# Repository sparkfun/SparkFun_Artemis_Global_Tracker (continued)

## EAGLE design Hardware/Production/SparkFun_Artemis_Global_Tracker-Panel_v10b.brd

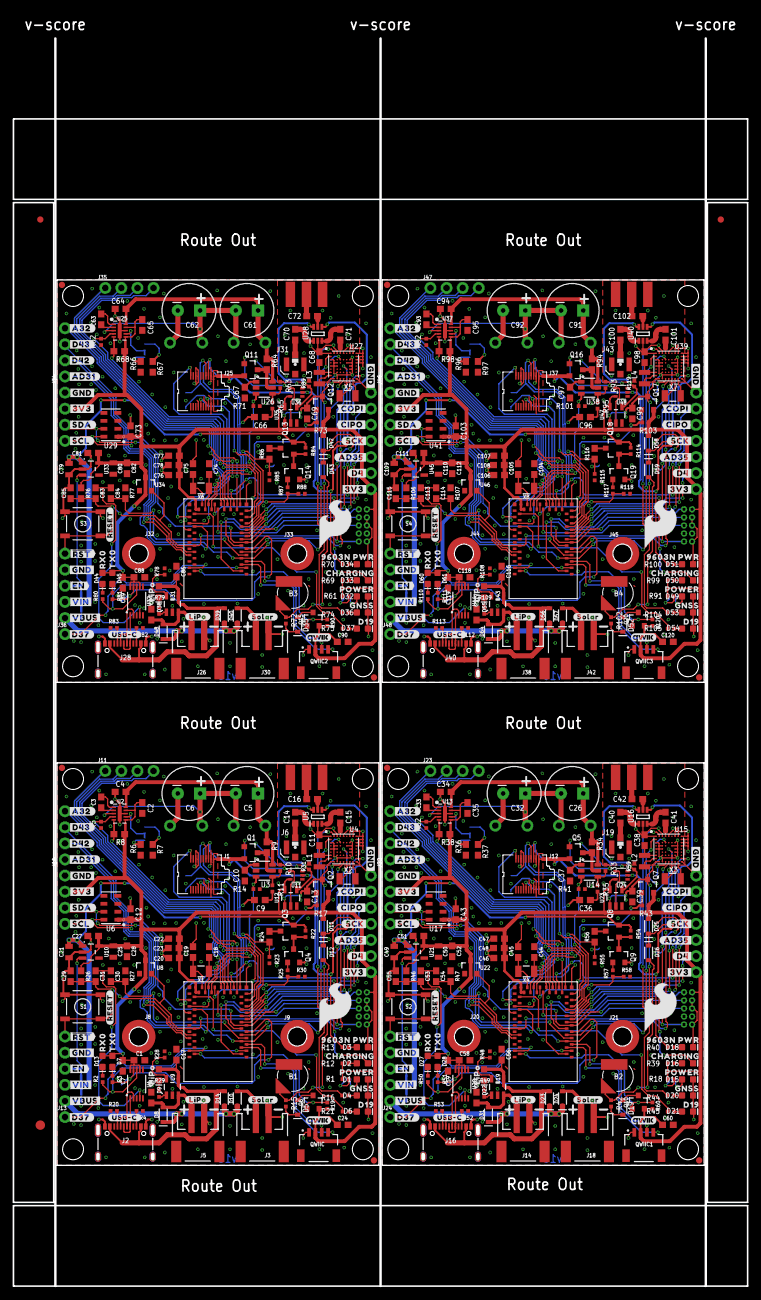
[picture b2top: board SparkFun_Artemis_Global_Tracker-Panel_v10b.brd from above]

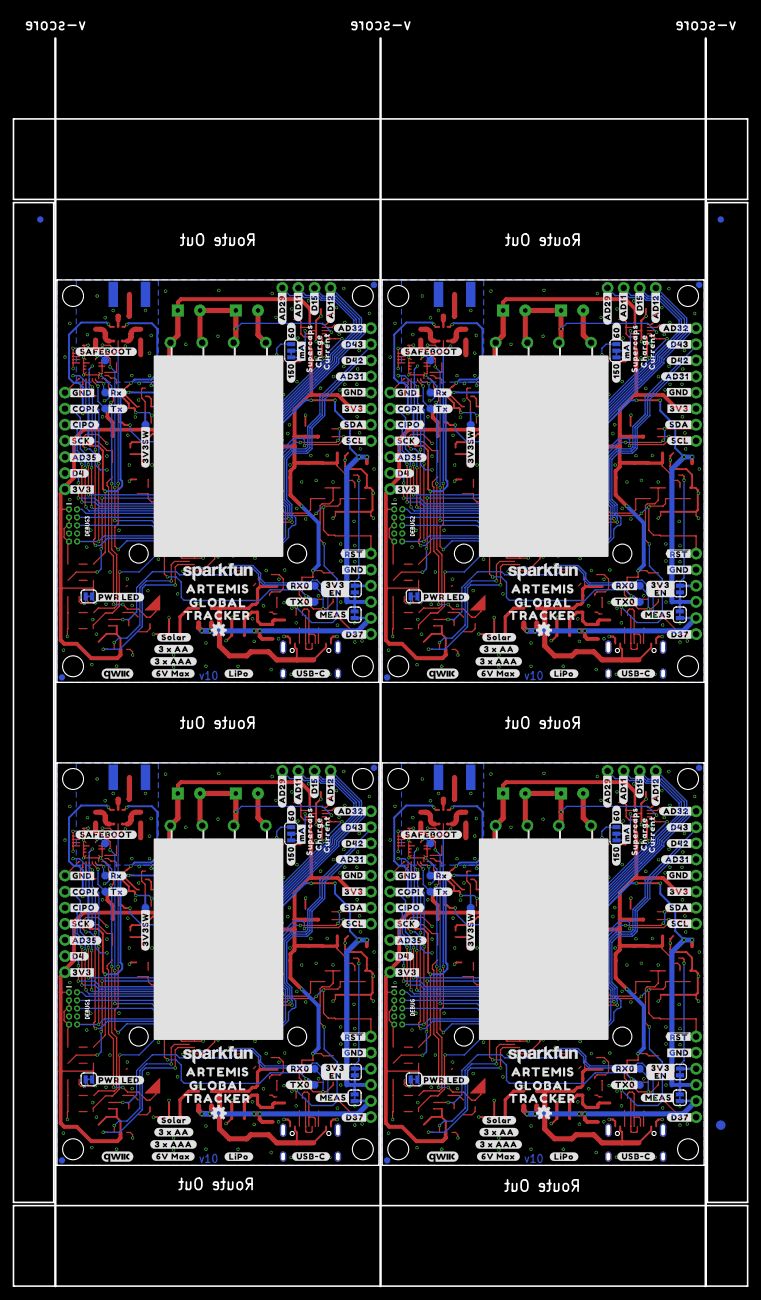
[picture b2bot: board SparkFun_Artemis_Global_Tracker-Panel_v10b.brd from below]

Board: 2 copper layers, 115.8 x 196.9 mm, 958 parts (319 on the bottom side), 404 nets.

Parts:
3V3EN, 3V3EN1, 3V3EN2, 3V3EN3: JUMPER-SMT_2_NC_TRACE_SILK; SMT-JUMPER_2_NC_TRACE_SILK
3V3SW, 3V3SW1, 3V3SW2, 3V3SW3: PAD.03X.05
5V1, 5V2, 5V3, 5V4: TEST-POINT3X5; PAD.03X.05
!RESET, !RESET1, !RESET2, !RESET3: 1X01_NO_SILK
B1, B2, B3, B4: ML414H_IV01E_BATTERY; ML414H_IV01E
C1, C9, C36, C58, C66, C88, C96, C118: 10nF; 0603
C2, C35, C65, C95: 2.2uF; 0603
C3, C10, C23, C24, C27, C33, C37, C48, C51, C60, C63, C67, C78, C81, C90, C93, C97, C108, C111, C120: 1.0uF; 0603
C4, C12, C34, C43, C64, C73, C94, C103: 0.22uF; 0603
C5, C6, C26, C32, C61, C62, C91, C92: 1F 2.7V; CPOL-RADIAL-1F-2.7V
C7, C13, C20, C28, C30, C31, C39, C46, C52, C53, C54, C59, C69, C76, C82, C83, C84, C89, C99, C106, C112, C113, C114, C119: 0.1uF; 0603
C8, C11, C17, C38, C56, C57, C68, C86, C87, C98, C116, C117: 4.7uF; 0603
C14, C15, C16, C40, C41, C42, C70, C71, C72, C100, C101, C102: 100pF; 0603
C18, C19, C44, C45, C74, C75, C104, C105: 15pF; 0603
C21, C25, C49, C50, C79, C80, C109, C110: 22uF; 0805
C22, C47, C77, C107: 10uF; 0603
C29, C55, C85, C115: 1nF; 0603
D1, D7, D15, D28, D32, D45, D49, D61: GREEN; LED-0603
D2, D9, D13, D16, D22, D27, D33, D38, D44, D50, D55, D60: Yellow; LED-0603
D3, D18, D34, D51: RED; LED-0603
D4, D20, D36, D53: BLUE; LED-0603
D5, D8, D10, D11, D12, D14, D19, D23, D24, D25, D26, D31, D35, D39, D40, D42, D43, D48, D52, D56, D57, D58, D59, D64: 0.5A/40V/420mV; SOD-323
D6, D21, D37, D54: WHITE; LED-0603
D17, D29, D30, D41, D46, D47, D62, D63: PAD.03X.05
DEBUG, DEBUG1, DEBUG2, DEBUG3: CORTEX_DEBUG; 2X5-PTH-1.27MM-NO_SILK
E$1, E$2, E$3, E$4: FIDUCIAL-1X2
E$5, E$6: FIDUCIAL-1.5X3
EN, EN1, EN2, EN3: 1X01_NO_SILK
GND, GND1, GND2, GND3: 1X01_NO_SILK
GPS_RX, GPS_RX1, GPS_RX2, GPS_RX3: TEST-POINT3X5; PAD.03X.05
GPS_TX, GPS_TX1, GPS_TX2, GPS_TX3: TEST-POINT3X5; PAD.03X.05
I2C, I2C1, I2C2, I2C3: PTH; 1X04_NO_SILK
J1, J12, J25, J37: IRIDIUM_9603N
J2, J16, J28, J40: USB-C; USB-C-16P-2LAYER-PADS
J3, J5, J14, J18, J26, J30, J38, J42: JST-2-SMD
J4, J15, J27, J39: 1X02_NO_SILK
J6, J19, J31, J43: U.FL
J7, J17, J29, J41: ANTENNA-GROUNDEDEDGE_SMA; SMA-EDGE
J8, J9, J20, J21, J32, J33, J44, J45: STAND-OFF-REFLOW-M2.0_6.0MM_TALL; STAND-OFF-REFLOW-M2.0
J10, J11, J22, J23, J34, J35, J46, J47: 1X04_NO_SILK
J13, J24, J36, J48: 1X01_NO_SILK
JP1, JP15, JP25, JP35: JUMPER-SMT_3_1-NC_TRACE_SILK; SMT-JUMPER_3_1-NC_TRACE_SILK
JP2, JP16, JP26, JP36: JUMPER-SMT_2_NC_TRACE_SILK; SMT-JUMPER_2_NC_TRACE_SILK
JP3, JP4, JP5, JP6, JP7, JP8, JP13, JP14, JP21, JP22, JP23, JP24, JP31, JP32, JP33, JP34: FIDUCIAL1X2; FIDUCIAL-1X2
JP9, JP10, JP11, JP12, JP17, JP18, JP19, JP20, JP27, JP28, JP29, JP30, JP37, JP38, JP39, JP40: STAND-OFF
L1, L2, L3, L4: 2.2uH; 0806
LOGO1, LOGO5, LOGO8, LOGO11: SFE_LOGO_NAME.1_INCH; SFE_LOGO_NAME_.1
LOGO2, LOGO6, LOGO9, LOGO12: SFE_LOGO_FLAME.3_INCH; SFE_LOGO_FLAME_.3
LOGO3, LOGO4, LOGO7, LOGO10: OSHW-LOGOMINI; OSHW-LOGO-MINI
MEAS, MEAS1, MEAS2, MEAS3: JUMPER-SMT_2_NC_TRACE_SILK; SMT-JUMPER_2_NC_TRACE_SILK
Q1, Q5, Q11, Q16: 5.8A/30V/35mΩ; SOT23-3
Q2, Q3, Q6, Q7, Q8, Q10, Q12, Q13, Q15, Q17, Q18, Q20: 20V/4.2A/52mΩ/1.4W; SOT23-3
Q4, Q9, Q14, Q19: 600mA/40V; SOT23-3
QWIIC, QWIIC1, QWIIC2, QWIIC3: QWIIC_RA; JST04_1MM_RA
R1, R18, R61, R91: 330; 0402-TIGHT
R2, R3, R12, R16, R21, R25, R29, R39, R44, R45, R49, R50, R51, R57, R69, R74, R75, R79, R80, R81, R87, R99, R104, R105, R109, R110, R111, R117: 1k; 0402-TIGHT
R4, R20, R52, R53, R82, R83, R112, R113: 5.1k; 0402-TIGHT
R5, R14, R17, R19, R22, R23, R30, R32, R41, R43, R54, R55, R58, R60, R62, R71, R73, R84, R85, R88, R90, R92, R101, R103, R114, R115, R118, R120: 10K; 0402-TIGHT
R6, R36, R66, R96: 12k; 0603
R7, R37, R67, R97: 30.1k; 0603
R8, R26, R38, R46, R68, R76, R98, R106: 100k; 0603
R9, R34, R64, R94: 0.015ohm; 0603
R10, R11, R33, R35, R63, R65, R93, R95: 100; 0402-TIGHT
R13, R28, R40, R48, R70, R78, R100, R108: 2.0K; 0402-TIGHT
R15, R42, R72, R102: 3.3K; 0402-TIGHT
R24, R56, R86, R116: 20k; 0603
R27, R47, R77, R107: 220k; 0603
R31, R59, R89, R119: 20k; 0402-TIGHT
RX0, RX1, RX2, RX3, RX4, RX5, RX6, RX7: TEST-POINT3X5; PAD.03X.05
S1, S2, S3, S4: RESET; TACTILE_SWITCH_SMD_5.2MM
SAFEBOOT, SAFEBOOT1, SAFEBOOT2, SAFEBOOT3: TEST-POINT3X5; PAD.03X.05
SC1+, SC1+1, SC1+2, SC1+3, SC1-, SC1-1, SC1-2, SC1-3, SC2+, SC2+1, SC2+2, SC2+3, SC2-, SC2-1, SC2-2, SC2-3: 1X01_NO_SILK
SPI, SPI1, SPI2, SPI3: 1X07_NO_SILK
TX0, TX1, TX2, TX3, TX4, TX5, TX6, TX7: TEST-POINT3X5; PAD.03X.05
U1, U20, U32, U44: CH340E_MSOP10; MSOP10
U2, U13, U25, U37: LTC3225EDDB; DFN300X200-10L
U3, U14, U26, U38: ADM4210_1TSOT6; TSOT6
U4, U15, U27, U39: U-BLOX_ZOE_M8Q-0-10; UBLOX_ZOE_M8-0-10
U5, U16, U28, U40: AS179-92LF; SOT65P220X100-6N
U6, U17, U29, U41: MS8607-02BA01
U7, U18, U30, U42: ARTEMIS_MODULESMD; ARTEMIS_FP
U8, U22, U34, U46: V_SUPERVISOR_BD48K24G_2.4V; SOT23-3
U9, U19, U31, U43: MCP73831; SOT23-5
U10, U21, U33, U45: 3.3V; SOT23-5
U11, U24, U36, U48: 74LVC1G04SE; SOT353
U12, U23, U35, U47: 74LVC1G08W5-7; SOT23-5
U$1, U$13, U$131, U$132, U$223, U$224, U$315, U$316: SUPERCAPACITOR151
U$2, U$177, U$269, U$361: #SCK#199608
U$3, U$43, U$111, U$124, U$203, U$216, U$295, U$308: #3V3#0
U$4, U$112, U$204, U$296: #SDA#0
U$5, U$117, U$209, U$301: #USB#C#0
U$6, U$113, U$205, U$297: #SCL#0
U$7, U$143, U$235, U$327: #VIN#158
U$8, U$98, U$190, U$282: #3V3SW#0
U$9, U$173, U$265, U$357: CHARGING9604
U$10, U$149, U$241, U$333: #COPI#9694
U$11, U$23, U$185, U$277: QWIIC_4MM
U$12, U$182, U$274, U$366: LIPO5
U$14, U$15, U$133, U$134, U$225, U$226, U$317, U$318: 10F_2#7V152
U$16, U$183, U$275, U$367: RX06
U$17, U$70, U$138, U$151, U$230, U$243, U$322, U$335: #3V3#153
U$18, U$184, U$276, U$368: TX07
U$19, U$178, U$270, U$362: #AD35#199609
U$20, U$36, U$110, U$125, U$202, U$217, U$294, U$309: #GND#0
U$21, U$139, U$231, U$323: #SDA#153
U$22, U$140, U$232, U$324: #SCL#154
U$24, U$152, U$244, U$336: #AD31#7
U$25, U$49, U$186, U$278: QWIIC_5MM
U$26, U$141, U$233, U$325: #_RST##156
U$27, U$142, U$234, U$326: #EN#157
U$28, U$99, U$191, U$283: #VIN#3#0
U$29, U$179, U$271, U$363: #AD35#0
U$30, U$62, U$187, U$279: ARTEMIS0
U$31, U$128, U$220, U$312: SUPERCAPS6
U$32, U$101, U$193, U$285: #D17#0
U$33, U$109, U$201, U$293: #SAFEBOOT#0
U$34, U$104, U$196, U$288: #TX0#0
U$35, U$106, U$198, U$290: #TX1#0
U$37, U$108, U$200, U$292: #RX#0
U$38, U$105, U$197, U$289: #RX1#0
U$39, U$107, U$199, U$291: #TX#0
U$40, U$100, U$192, U$284: #5#3V#0
U$41, U$102, U$194, U$286: #D41#0
U$42, U$103, U$195, U$287: #RX0#0
U$44, U$146, U$238, U$330: #RESET#162
U$45, U$148, U$240, U$332: #SOLAR#165
U$46, U$147, U$239, U$331: #LIPO#164
U$47, U$114, U$206, U$298: #MEAS#0
U$48, U$115, U$207, U$299: #3V3_#0
U$50, U$180, U$272, U$364: #D4#36
U$51, U$68, U$188, U$280: GLOBAL0
U$52, U$97, U$189, U$281: TRACKER0
U$53, U$118, U$210, U$302: #LIPO#0
U$54, U$116, U$208, U$300: #_EN_#0
U$55, U$119, U$211, U$303: #SOLAR#0
U$56, U$145, U$237, U$329: #USB#C#161
U$57, U$120, U$212, U$304: #3_X_AA#0
U$58, U$144, U$236, U$328: #VBUS#159
U$59, U$167, U$259, U$351: #AD32#152
U$60, U$150, U$242, U$334: #SCK#9696
U$61, U$123, U$215, U$307: #PWR_LED#0
U$63, U$181, U$273, U$365: #D4#5
U$64, U$126, U$218, U$310: #CIPO#2
U$65, U$121, U$213, U$305: #3_X_AAA#0
U$66, U$122, U$214, U$306: #6V_MAX#0
U$67, U$129, U$221, U$313: CHARGE8
U$69, U$130, U$222, U$314: CURRENT9
U$71, U$153, U$245, U$337: #D42#32
U$72, U$168, U$260, U$352: #D37#152
U$73, U$154, U$246, U$338: #D43#43
U$74, U$158, U$250, U$342: #150#61
U$75, U$127, U$219, U$311: #COPI#5
U$76, U$77, U$78, U$135, U$136, U$137, U$227, U$228, U$229, U$319, U$320, U$321: #GND#152
U$79, U$155, U$247, U$339: #A32#44
U$80, U$156, U$248, U$340: #MA#45
U$81, U$157, U$249, U$341: #60#46
U$82, U$159, U$251, U$343: #D43#151
U$83, U$160, U$252, U$344: #D42#151
U$84, U$161, U$253, U$345: #AD31#151
U$85, U$162, U$254, U$346: #AD12#151
U$86, U$163, U$255, U$347: #D15#151
U$87, U$164, U$256, U$348: #AD11#151
U$88, U$165, U$257, U$349: #AD29#151
U$89, U$166, U$258, U$350: #CIPO#151
U$90, U$169, U$261, U$353: #D37#0
U$91, U$170, U$262, U$354: #GND#38
U$92, U$171, U$263, U$355: ##RST##39
U$93, U$172, U$264, U$356: 9603N_PWR40
U$94, U$174, U$266, U$358: POWER9605
U$95, U$175, U$267, U$359: GNSS9606
U$96, U$176, U$268, U$360: D199607
VIN/1, VIN/2, VIN/3, VIN/4: TEST-POINT3X5; PAD.03X.05
X1, X2, X3, X4, X5, X6, X7, X8: 32.768kHz; CRYSTAL-SMD-3.2X1.5MM

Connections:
3.3V: C1.1, C2.1, C7.1, C12.1, C20.2, C22.1, C23.1, C24.1, C25.1, C27.1, C28.1, D7.A, D11.A, D13.A, DEBUG.1, I2C.2, Q2.2, Q6.2, QWIIC.2, R1.2, R8.2, R12.2, R17.2, R19.2, R26.2, SPI.7, U1.7, U1.10, U2.6, U2.9, U6.1, U7.VDD@36, U7.VDD@37, U8.3, U10.5, U11.5, U12.5
3.3V1: C35.1, C43.1, C46.2, C47.1, C48.1, C50.1, C51.1, C52.1, C58.1, C59.1, C60.1, D25.A, D27.A, D28.A, DEBUG1.1, I2C1.2, Q7.2, Q10.2, QWIIC1.2, R18.2, R38.2, R39.2, R43.2, R46.2, R60.2, SPI1.7, U13.6, U13.9, U17.1, U18.VDD@36, U18.VDD@37, U20.7, U20.10, U21.5, U22.3, U23.5, U24.5
3.3V2: C65.1, C73.1, C76.2, C77.1, C78.1, C80.1, C81.1, C82.1, C88.1, C89.1, C90.1, D42.A, D44.A, D45.A, DEBUG2.1, I2C2.2, Q12.2, Q15.2, QWIIC2.2, R61.2, R68.2, R69.2, R73.2, R76.2, R90.2, SPI2.7, U25.6, U25.9, U29.1, U30.VDD@36, U30.VDD@37, U32.7, U32.10, U33.5, U34.3, U35.5, U36.5
3.3V3: C95.1, C103.1, C106.2, C107.1, C108.1, C110.1, C111.1, C112.1, C118.1, C119.1, C120.1, D58.A, D60.A, D61.A, DEBUG3.1, I2C3.2, Q17.2, Q20.2, QWIIC3.2, R91.2, R98.2, R99.2, R103.2, R106.2, R120.2, SPI3.7, U37.6, U37.9, U41.1, U42.VDD@36, U42.VDD@37, U44.7, U44.10, U45.5, U46.3, U47.5, U48.5
3V3SW: 3V3SW.1, C13.1, Q2.3, R16.2, U4.24, U4.25, U12.1
3V3SW1: 3V3SW1.1, C39.1, Q7.3, R44.2, U15.24, U15.25, U23.1
3V3SW2: 3V3SW2.1, C69.1, Q12.3, R74.2, U27.24, U27.25, U35.1
3V3SW3: 3V3SW3.1, C99.1, Q17.3, R104.2, U39.24, U39.25, U47.1
ANTENNA: C16.1, J7.SIG
ANTENNA1: C42.1, J17.SIG
ANTENNA2: C72.1, J29.SIG
ANTENNA3: C102.1, J41.SIG
ARTEMIS_!RESET: !RESET.1, C29.1, C31.2, DEBUG.10, R26.1, S1.3, S1.4, U4.20, U7.~RST, U8.2
ARTEMIS_!RESET1: !RESET1.1, C53.2, C55.1, DEBUG1.10, R46.1, S2.3, S2.4, U15.20, U18.~RST, U22.2
ARTEMIS_!RESET2: !RESET2.1, C83.2, C85.1, DEBUG2.10, R76.1, S3.3, S3.4, U27.20, U30.~RST, U34.2
ARTEMIS_!RESET3: !RESET3.1, C113.2, C115.1, DEBUG3.10, R106.1, S4.3, S4.4, U39.20, U42.~RST, U46.2
ARTEMIS_!RTS!: C30.1, C31.1, U1.4
ARTEMIS_!RTS!1: C53.1, C54.1, U20.4
ARTEMIS_!RTS!2: C83.1, C84.1, U32.4
ARTEMIS_!RTS!3: C113.1, C114.1, U44.4
ARTEMIS_AD1: J22.1, U18.~AD31
ARTEMIS_AD2: J23.4, U18.~AD29
ARTEMIS_AD3: J23.3, U18.~AD11
ARTEMIS_AD4: J23.1, U18.~AD12
ARTEMIS_AD5: J22.4, U18.~AD32
ARTEMIS_AD6: J34.1, U30.~AD31
ARTEMIS_AD7: J35.4, U30.~AD29
ARTEMIS_AD8: J35.3, U30.~AD11
ARTEMIS_AD9: J35.1, U30.~AD12
ARTEMIS_AD10: J34.4, U30.~AD32
ARTEMIS_AD11: J11.3, U7.~AD11
ARTEMIS_AD12: J11.1, U7.~AD12
ARTEMIS_AD13: J46.1, U42.~AD31
ARTEMIS_AD14: J47.4, U42.~AD29
ARTEMIS_AD15: J47.3, U42.~AD11
ARTEMIS_AD16: J47.1, U42.~AD12
ARTEMIS_AD17: J46.4, U42.~AD32
ARTEMIS_AD29: J11.4, U7.~AD29
ARTEMIS_AD31: J10.1, U7.~AD31
ARTEMIS_AD32: J10.4, U7.~AD32
ARTEMIS_BOOT: C30.2, R27.2, U7.BOOT
ARTEMIS_BOOT1: C54.2, R47.2, U18.BOOT
ARTEMIS_BOOT2: C84.2, R77.2, U30.BOOT
ARTEMIS_BOOT3: C114.2, R107.2, U42.BOOT
ARTEMIS_D1: DEBUG1.6, U18.~AD33/SWO
ARTEMIS_D2: SPI1.5, U18.~AD35
ARTEMIS_D3: R55.1, R56.2, U18.~AD13, VIN/1.1
ARTEMIS_D4: SPI.6, U7.~D4
ARTEMIS_D5: R45.2, U18.~D19
ARTEMIS_D5_SCK: SPI.4, U7.~D5
ARTEMIS_D5_SCK1: SPI1.4, U18.~D5
ARTEMIS_D5_SCK2: SPI2.4, U30.~D5
ARTEMIS_D5_SCK3: SPI3.4, U42.~D5
ARTEMIS_D6: J12.19, U18.~D18
ARTEMIS_D6_MISO: SPI.3, U7.~D6
ARTEMIS_D6_MISO1: SPI1.3, U18.~D6
ARTEMIS_D6_MISO2: SPI2.3, U30.~D6
ARTEMIS_D6_MISO3: SPI3.3, U42.~D6
ARTEMIS_D7: J12.7, RX3.1, U18.~D25
ARTEMIS_D7_MOSI: SPI.2, U7.D7
ARTEMIS_D7_MOSI1: SPI1.2, U18.D7
ARTEMIS_D7_MOSI2: SPI2.2, U30.D7
ARTEMIS_D7_MOSI3: SPI3.2, U42.D7
ARTEMIS_D8: R32.2, U13.4, U18.~D27
ARTEMIS_D8_SCL: I2C.4, U4.32, U6.8, U7.D8
ARTEMIS_D8_SCL1: I2C1.4, U15.32, U17.8, U18.D8
ARTEMIS_D8_SCL2: I2C2.4, U27.32, U29.8, U30.D8
ARTEMIS_D8_SCL3: I2C3.4, U39.32, U41.8, U42.D8
ARTEMIS_D9: SPI1.6, U18.~D4
ARTEMIS_D9_SDA: I2C.3, U4.2, U6.7, U7.D9
ARTEMIS_D9_SDA1: I2C1.3, U15.2, U17.7, U18.D9
ARTEMIS_D9_SDA2: I2C2.3, U27.2, U29.7, U30.D9
ARTEMIS_D9_SDA3: I2C3.3, U39.2, U41.7, U42.D9
ARTEMIS_D10: U4.50, U7.D10
ARTEMIS_D11: U15.50, U18.D10
ARTEMIS_D12: D29.1, J12.5, U18.D17
ARTEMIS_D13: R23.1, R24.2, U7.~AD13, VIN/3.1
ARTEMIS_D14: R41.1, U14.3, U18.~D22
ARTEMIS_D15: J11.2, U7.D15
ARTEMIS_D16: J12.6, TX3.1, U18.~D24
ARTEMIS_D17: D17.1, J1.5, U7.D17
ARTEMIS_D18: J1.19, U7.~D18
ARTEMIS_D19: R21.2, U7.~D19
ARTEMIS_D20: Q7.1, R43.1, U18.~D26
ARTEMIS_D21: D16.C, R38.1, U13.5, U18.~D28
ARTEMIS_D22: R14.1, U3.3, U7.~D22
ARTEMIS_D23: D30.1, J12.12, U18.D41
ARTEMIS_D24: J1.6, TX1.1, U7.~D24
ARTEMIS_D25: J1.7, RX1.1, U7.~D25
ARTEMIS_D26: Q2.1, R17.1, U7.~D26
ARTEMIS_D27: R5.2, U2.4, U7.~D27
ARTEMIS_D28: D2.C, R8.1, U2.5, U7.~D28
ARTEMIS_D29: R57.1, R58.1, U18.AD34
ARTEMIS_D30: Q10.1, R60.1, U18.~D44
ARTEMIS_D31: J22.2, U18.~D42
ARTEMIS_D32: J22.3, U18.~D43
ARTEMIS_D33: DEBUG.6, U7.~AD33/SWO
ARTEMIS_D34: R25.1, R30.1, U7.AD34
ARTEMIS_D35: SPI.5, U7.~AD35
ARTEMIS_D36: J23.2, U18.D15
ARTEMIS_D37: J13.1, U7.~D37
ARTEMIS_D38: J24.1, U18.~D37
ARTEMIS_D39: DEBUG2.6, U30.~AD33/SWO
ARTEMIS_D39_SCL1: QWIIC1.4, U18.~D39
ARTEMIS_D39_SCL2: QWIIC2.4, U30.~D39
ARTEMIS_D39_SCL3: QWIIC3.4, U42.~D39
ARTEMIS_D39_SCL4: QWIIC.4, U7.~D39
ARTEMIS_D40: SPI2.5, U30.~AD35
ARTEMIS_D40_SDA1: QWIIC1.3, U18.D40
ARTEMIS_D40_SDA2: QWIIC2.3, U30.D40
ARTEMIS_D40_SDA3: QWIIC3.3, U42.D40
ARTEMIS_D40_SDA4: QWIIC.3, U7.D40
ARTEMIS_D41: D41.1, J1.12, U7.D41
ARTEMIS_D42: J10.2, U7.~D42
ARTEMIS_D43: J10.3, U7.~D43
ARTEMIS_D44: Q6.1, R19.1, U7.~D44
ARTEMIS_D45: R85.1, R86.2, U30.~AD13, VIN/2.1
ARTEMIS_D46: R75.2, U30.~D19
ARTEMIS_D47: J25.19, U30.~D18
ARTEMIS_D48: J25.7, RX5.1, U30.~D25
ARTEMIS_D49: R62.2, U25.4, U30.~D27
ARTEMIS_D50: SPI2.6, U30.~D4
ARTEMIS_D51: U27.50, U30.D10
ARTEMIS_D52: D46.1, J25.5, U30.D17
ARTEMIS_D53: R71.1, U26.3, U30.~D22
ARTEMIS_D54: J25.6, TX5.1, U30.~D24
ARTEMIS_D55: Q12.1, R73.1, U30.~D26
ARTEMIS_D56: D33.C, R68.1, U25.5, U30.~D28
ARTEMIS_D57: D47.1, J25.12, U30.D41
ARTEMIS_D58: R87.1, R88.1, U30.AD34
ARTEMIS_D59: Q15.1, R90.1, U30.~D44
ARTEMIS_D60: J34.2, U30.~D42
ARTEMIS_D61: J34.3, U30.~D43
ARTEMIS_D62: J35.2, U30.D15
ARTEMIS_D63: J36.1, U30.~D37
ARTEMIS_D64: DEBUG3.6, U42.~AD33/SWO
ARTEMIS_D65: SPI3.5, U42.~AD35
ARTEMIS_D66: R115.1, R116.2, U42.~AD13, VIN/4.1
ARTEMIS_D67: R105.2, U42.~D19
ARTEMIS_D68: J37.19, U42.~D18
ARTEMIS_D69: J37.7, RX7.1, U42.~D25
ARTEMIS_D70: R92.2, U37.4, U42.~D27
ARTEMIS_D71: SPI3.6, U42.~D4
ARTEMIS_D72: U39.50, U42.D10
ARTEMIS_D73: D62.1, J37.5, U42.D17
ARTEMIS_D74: R101.1, U38.3, U42.~D22
ARTEMIS_D75: J37.6, TX7.1, U42.~D24
ARTEMIS_D76: Q17.1, R103.1, U42.~D26
ARTEMIS_D77: D50.C, R98.1, U37.5, U42.~D28
ARTEMIS_D78: D63.1, J37.12, U42.D41
ARTEMIS_D79: R117.1, R118.1, U42.AD34
ARTEMIS_D80: Q20.1, R120.1, U42.~D44
ARTEMIS_D81: J46.2, U42.~D42
ARTEMIS_D82: J46.3, U42.~D43
ARTEMIS_D83: J47.2, U42.D15
ARTEMIS_D84: J48.1, U42.~D37
ARTEMIS_RX0: R2.1, RX0.1, U1.8, U7.RXI-0
ARTEMIS_RX1: R50.1, RX2.1, U18.RXI-0, U20.8
ARTEMIS_RX2: R80.1, RX4.1, U30.RXI-0, U32.8
ARTEMIS_RX3: R110.1, RX6.1, U42.RXI-0, U44.8
ARTEMIS_SWDCK: DEBUG.4, U7.SWDCK
ARTEMIS_SWDCK1: DEBUG1.4, U18.SWDCK
ARTEMIS_SWDCK2: DEBUG2.4, U30.SWDCK
ARTEMIS_SWDCK3: DEBUG3.4, U42.SWDCK
ARTEMIS_SWDIO: DEBUG.2, U7.SWDIO
ARTEMIS_SWDIO1: DEBUG1.2, U18.SWDIO
ARTEMIS_SWDIO2: DEBUG2.2, U30.SWDIO
ARTEMIS_SWDIO3: DEBUG3.2, U42.SWDIO
ARTEMIS_TX0: R3.1, TX0.1, U1.9, U7.TXO-0
ARTEMIS_TX1: R51.1, TX2.1, U18.TXO-0, U20.9
ARTEMIS_TX2: R81.1, TX4.1, U30.TXO-0, U32.9
ARTEMIS_TX3: R111.1, TX6.1, U42.TXO-0, U44.9
CC1: J16.B5, R52.2
CC2: J16.A5, R53.2
CC3: J2.B5, R4.2
CC4: J2.A5, R20.2
CC5: J28.B5, R82.2
CC6: J28.A5, R83.2
CC7: J40.B5, R112.2
CC8: J40.A5, R113.2
D+1: J16.A6, J16.B6, U20.1
D+2: J2.A6, J2.B6, U1.1
D+3: J28.A6, J28.B6, U32.1
D+4: J40.A6, J40.B6, U44.1
D-1: J16.A7, J16.B7, U20.2
D-2: J2.A7, J2.B7, U1.2
D-3: J28.A7, J28.B7, U32.2
D-4: J40.A7, J40.B7, U44.2
EXT_PWR: 5V3.1, J1.1, J1.2, Q1.2, R13.2, U5.4, U11.2
EXT_PWR1: 5V1.1, J12.1, J12.2, Q5.2, R40.2, U16.4, U24.2
EXT_PWR2: 5V2.1, J25.1, J25.2, Q11.2, R70.2, U28.4, U36.2
EXT_PWR3: 5V4.1, J37.1, J37.2, Q16.2, R100.2, U40.4, U48.2
GND: B1.-, C1.2, C2.2, C4.2, C6.-, C7.2, C8.2, C9.2, C10.2, C11.2, C12.2, C13.2, C17.2, C18.1, C19.1, C20.1, C21.2, C22.2, C23.2, C24.2, C25.2, C27.2, C28.2, C29.2, D1.C, D3.C, D4.C, D6.C, DEBUG.3, DEBUG.5, DEBUG.9, GND.1, I2C.1, J1.3, J1.4, J1.8, J1.13, J1.14, J1.15, J1.18, J2.GND, J2.GND2, J3.1, J5.1, J6.1, J6.2, J7.GND@0, J7.GND@1, J7.GND@2, J7.GND@3, J8.1, J9.1, Q4.2, QWIIC.1, R4.1, R5.1, R6.1, R7.2, R14.2, R20.1, R23.2, R27.1, R28.1, R30.2, R31.2, S1.1, S1.2, SC2-.1, SPI.1, U1.3, U2.8, U2.11, U3.2, U4.1, U4.3, U4.5, U4.7, U4.8, U4.9, U4.10, U4.11, U4.12, U4.17, U4.23, U4.29, U4.31, U4.37, U4.38, U4.39, U4.40, U4.41, U4.44, U4.46, U4.47, U4.49, U5.2, U6.3, U7.GND@1, U7.GND@22, U7.GND@38, U7.GND@39, U7.GND@47, U7.GND@59, U8.1, U9.2, U10.2, U11.3, U12.3
GND1: B2.-, C32.-, C34.2, C35.2, C36.2, C37.2, C38.2, C39.2, C43.2, C44.1, C45.1, C46.1, C47.2, C48.2, C49.2, C50.2, C51.2, C52.2, C55.2, C56.2, C57.2, C58.2, C59.2, C60.2, D15.C, D18.C, D20.C, D21.C, DEBUG1.3, DEBUG1.5, DEBUG1.9, GND1.1, I2C1.1, J12.3, J12.4, J12.8, J12.13, J12.14, J12.15, J12.18, J14.1, J16.GND, J16.GND2, J17.GND@0, J17.GND@1, J17.GND@2, J17.GND@3, J18.1, J19.1, J19.2, J20.1, J21.1, Q9.2, QWIIC1.1, R32.1, R36.1, R37.2, R41.2, R47.1, R48.1, R52.1, R53.1, R55.2, R58.2, R59.2, S2.1, S2.2, SC2-1.1, SPI1.1, U13.8, U13.11, U14.2, U15.1, U15.3, U15.5, U15.7, U15.8, U15.9, U15.10, U15.11, U15.12, U15.17, U15.23, U15.29, U15.31, U15.37, U15.38, U15.39, U15.40, U15.41, U15.44, U15.46, U15.47, U15.49, U16.2, U17.3, U18.GND@1, U18.GND@22, U18.GND@38, U18.GND@39, U18.GND@47, U18.GND@59, U19.2, U20.3, U21.2, U22.1, U23.3, U24.3
GND2: B3.-, C62.-, C64.2, C65.2, C66.2, C67.2, C68.2, C69.2, C73.2, C74.1, C75.1, C76.1, C77.2, C78.2, C79.2, C80.2, C81.2, C82.2, C85.2, C86.2, C87.2, C88.2, C89.2, C90.2, D32.C, D34.C, D36.C, D37.C, DEBUG2.3, DEBUG2.5, DEBUG2.9, GND2.1, I2C2.1, J25.3, J25.4, J25.8, J25.13, J25.14, J25.15, J25.18, J26.1, J28.GND, J28.GND2, J29.GND@0, J29.GND@1, J29.GND@2, J29.GND@3, J30.1, J31.1, J31.2, J32.1, J33.1, Q14.2, QWIIC2.1, R62.1, R66.1, R67.2, R71.2, R77.1, R78.1, R82.1, R83.1, R85.2, R88.2, R89.2, S3.1, S3.2, SC2-2.1, SPI2.1, U25.8, U25.11, U26.2, U27.1, U27.3, U27.5, U27.7, U27.8, U27.9, U27.10, U27.11, U27.12, U27.17, U27.23, U27.29, U27.31, U27.37, U27.38, U27.39, U27.40, U27.41, U27.44, U27.46, U27.47, U27.49, U28.2, U29.3, U30.GND@1, U30.GND@22, U30.GND@38, U30.GND@39, U30.GND@47, U30.GND@59, U31.2, U32.3, U33.2, U34.1, U35.3, U36.3
GND3: B4.-, C92.-, C94.2, C95.2, C96.2, C97.2, C98.2, C99.2, C103.2, C104.1, C105.1, C106.1, C107.2, C108.2, C109.2, C110.2, C111.2, C112.2, C115.2, C116.2, C117.2, C118.2, C119.2, C120.2, D49.C, D51.C, D53.C, D54.C, DEBUG3.3, DEBUG3.5, DEBUG3.9, GND3.1, I2C3.1, J37.3, J37.4, J37.8, J37.13, J37.14, J37.15, J37.18, J38.1, J40.GND, J40.GND2, J41.GND@0, J41.GND@1, J41.GND@2, J41.GND@3, J42.1, J43.1, J43.2, J44.1, J45.1, Q19.2, QWIIC3.1, R92.1, R96.1, R97.2, R101.2, R107.1, R108.1, R112.1, R113.1, R115.2, R118.2, R119.2, S4.1, S4.2, SC2-3.1, SPI3.1, U37.8, U37.11, U38.2, U39.1, U39.3, U39.5, U39.7, U39.8, U39.9, U39.10, U39.11, U39.12, U39.17, U39.23, U39.29, U39.31, U39.37, U39.38, U39.39, U39.40, U39.41, U39.44, U39.46, U39.47, U39.49, U40.2, U41.3, U42.GND@1, U42.GND@22, U42.GND@38, U42.GND@39, U42.GND@47, U42.GND@59, U43.2, U44.3, U45.2, U46.1, U47.3, U48.3
GNSS: C15.2, U4.4
GNSS1: C41.2, U15.4
GNSS2: C71.2, U27.4
GNSS3: C101.2, U39.4
IRIDIUM: C14.2, J6.FEED
IRIDIUM1: C40.2, J19.FEED
IRIDIUM2: C70.2, J31.FEED
IRIDIUM3: C100.2, J43.FEED
LTC3225_VOUT: C4.1, C5.+, R9.2, SC1+.1, U2.10, U3.6
LTC3225_VOUT1: C26.+, C34.1, R34.2, SC1+1.1, U13.10, U14.6
LTC3225_VOUT2: C61.+, C64.1, R64.2, SC1+2.1, U25.10, U26.6
LTC3225_VOUT3: C91.+, C94.1, R94.2, SC1+3.1, U37.10, U38.6
unnamed: C5.-, C6.+, SC1-.1, SC2+.1, U2.3
unnamed: JP1.3, R6.2
unnamed: JP2.2, R1.1
unnamed: JP1.1, R7.1
unnamed: D2.A, R12.1
unnamed: D3.A, R13.1
unnamed: D5.A, Q6.3
unnamed: Q1.3, R9.1, U3.5
unnamed: C3.2, U2.2
unnamed: C3.1, U2.1
unnamed: JP1.2, U2.7
unnamed: Q1.1, R10.1
unnamed: R10.2, R11.1, U3.4
unnamed: C9.1, R11.2
unnamed: C10.1, U3.1
unnamed: L1.2, U4.26
unnamed: C11.1, L1.1, U4.27
unnamed: U4.18, X2.P$2
unnamed: U4.19, X2.P$1
unnamed: D5.C, R15.2
unnamed: D4.A, R16.1
unnamed: D13.C, R2.2
unnamed: D1.A, JP2.1
unnamed: D11.C, D12.C, U4.16
unnamed: SAFEBOOT.1, U4.34
unnamed: GPS_RX.1, U4.22
unnamed: GPS_TX.1, U4.21
unnamed: C14.1, U5.1
unnamed: C15.1, U5.3
unnamed: C16.2, U5.5
unnamed: R31.1, U5.6, U12.4
unnamed: D7.C, R3.2
unnamed: U11.4, U12.2
unnamed: C33.2, U13.2
unnamed: D6.A, R21.1
unnamed: 3V3EN.2, EN.1, U10.3
unnamed: Q3.1, Q4.3, R22.1
unnamed: C33.1, U13.1
unnamed: R28.2, U9.5
unnamed: D9.C, R29.2
unnamed: R29.1, U9.1
unnamed: JP15.2, U13.7
unnamed: C26.-, C32.+, SC1-1.1, SC2+1.1, U13.3
unnamed: JP15.3, R36.2
unnamed: JP15.1, R37.1
unnamed: Q3.3, R24.1
unnamed: Q4.1, R25.2
unnamed: D16.A, R39.1
unnamed: D18.A, R40.1
unnamed: Q5.3, R34.1, U14.5
unnamed: Q5.1, R33.1
unnamed: R33.2, R35.1, U14.4
unnamed: C36.1, R35.2
unnamed: C37.1, U14.1
unnamed: L2.2, U15.26
unnamed: C38.1, L2.1, U15.27
unnamed: U15.18, X3.P$2
unnamed: U15.19, X3.P$1
unnamed: D19.C, R42.2
unnamed: SAFEBOOT1.1, U15.34
unnamed: GPS_RX1.1, U15.22
unnamed: GPS_TX1.1, U15.21
unnamed: C40.1, U16.1
unnamed: C41.1, U16.3
unnamed: C42.2, U16.5
unnamed: D20.A, R44.1
unnamed: D21.A, R45.1
unnamed: R48.2, U19.5
unnamed: D22.C, R49.2
unnamed: R49.1, U19.1
unnamed: D25.C, D26.C, U15.16
unnamed: 3V3EN1.2, EN1.1, U21.3
unnamed: Q8.1, Q9.3, R54.1
unnamed: Q8.3, R56.1
unnamed: Q9.1, R57.2
unnamed: D27.C, R50.2
unnamed: D28.C, R51.2
unnamed: JP16.2, R18.1
unnamed: D15.A, JP16.1
unnamed: R59.1, U16.6, U23.4
unnamed: U23.2, U24.4
unnamed: D19.A, Q10.3
unnamed: C63.2, U25.2
unnamed: C63.1, U25.1
unnamed: JP25.2, U25.7
unnamed: C61.-, C62.+, SC1-2.1, SC2+2.1, U25.3
unnamed: JP25.3, R66.2
unnamed: JP25.1, R67.1
unnamed: D33.A, R69.1
unnamed: D34.A, R70.1
unnamed: Q11.3, R64.1, U26.5
unnamed: Q11.1, R63.1
unnamed: R63.2, R65.1, U26.4
unnamed: C66.1, R65.2
unnamed: C67.1, U26.1
unnamed: L3.2, U27.26
unnamed: C68.1, L3.1, U27.27
unnamed: U27.18, X5.P$2
unnamed: U27.19, X5.P$1
unnamed: D35.C, R72.2
unnamed: SAFEBOOT2.1, U27.34
unnamed: GPS_RX2.1, U27.22
unnamed: GPS_TX2.1, U27.21
unnamed: C70.1, U28.1
unnamed: C71.1, U28.3
unnamed: C72.2, U28.5
unnamed: D36.A, R74.1
unnamed: D37.A, R75.1
unnamed: R78.2, U31.5
unnamed: D38.C, R79.2
unnamed: R79.1, U31.1
unnamed: D42.C, D43.C, U27.16
unnamed: 3V3EN2.2, EN2.1, U33.3
unnamed: Q13.1, Q14.3, R84.1
unnamed: Q13.3, R86.1
unnamed: Q14.1, R87.2
unnamed: D44.C, R80.2
unnamed: D45.C, R81.2
unnamed: JP26.2, R61.1
unnamed: D32.A, JP26.1
unnamed: R89.1, U28.6, U35.4
unnamed: U35.2, U36.4
unnamed: D35.A, Q15.3
unnamed: C93.2, U37.2
unnamed: C93.1, U37.1
unnamed: JP35.2, U37.7
unnamed: C91.-, C92.+, SC1-3.1, SC2+3.1, U37.3
unnamed: JP35.3, R96.2
unnamed: JP35.1, R97.1
unnamed: D50.A, R99.1
unnamed: D51.A, R100.1
unnamed: Q16.3, R94.1, U38.5
unnamed: Q16.1, R93.1
unnamed: R93.2, R95.1, U38.4
unnamed: C96.1, R95.2
unnamed: C97.1, U38.1
unnamed: L4.2, U39.26
unnamed: C98.1, L4.1, U39.27
unnamed: U39.18, X7.P$2
unnamed: U39.19, X7.P$1
unnamed: D52.C, R102.2
unnamed: SAFEBOOT3.1, U39.34
unnamed: GPS_RX3.1, U39.22
unnamed: GPS_TX3.1, U39.21
unnamed: C100.1, U40.1
unnamed: C101.1, U40.3
unnamed: C102.2, U40.5
unnamed: D53.A, R104.1
unnamed: D54.A, R105.1
unnamed: R108.2, U43.5
unnamed: D55.C, R109.2
unnamed: R109.1, U43.1
unnamed: D58.C, D59.C, U39.16
unnamed: 3V3EN3.2, EN3.1, U45.3
unnamed: Q18.1, Q19.3, R114.1
unnamed: Q18.3, R116.1
unnamed: Q19.1, R117.2
unnamed: D60.C, R110.2
unnamed: D61.C, R111.2
unnamed: JP36.2, R91.1
unnamed: D49.A, JP36.1
unnamed: R119.1, U40.6, U47.4
unnamed: U47.2, U48.4
unnamed: D52.A, Q20.3
VBUS: D8.C, D10.C, D14.C, J4.2, MEAS.1
VBUS1: D23.C, D24.C, D31.C, J15.2, MEAS1.1
VBUS2: D39.C, D40.C, D48.C, J27.2, MEAS2.1
VBUS3: D56.C, D57.C, D64.C, J39.2, MEAS3.1
VIN: 3V3EN.1, C21.1, J4.1, MEAS.2, Q3.2, R22.2, U10.1
VIN1: 3V3EN1.1, C49.1, J15.1, MEAS1.2, Q8.2, R54.2, U21.1
VIN2: 3V3EN2.1, C79.1, J27.1, MEAS2.2, Q13.2, R84.2, U33.1
VIN3: 3V3EN3.1, C109.1, J39.1, MEAS3.2, Q18.2, R114.2, U45.1
V_AAA: D10.A, J3.2
V_AAA1: D24.A, J18.2
V_AAA2: D40.A, J30.2
V_AAA3: D57.A, J42.2
V_BATT: C8.1, D8.A, J5.2, U9.3
V_BATT1: C57.1, D31.A, J14.2, U19.3
V_BATT2: C87.1, D48.A, J26.2, U31.3
V_BATT3: C117.1, D64.A, J38.2, U43.3
V_BCKP: B1.+, D12.A, R15.1
V_BCKP1: B2.+, D26.A, R42.1
V_BCKP2: B3.+, D43.A, R72.1
V_BCKP3: B4.+, D59.A, R102.1
V_USB: C17.1, D9.A, D14.A, J2.VBUS1, J2.VBUS2, U9.4
V_USB1: C56.1, D22.A, D23.A, J16.VBUS1, J16.VBUS2, U19.4
V_USB2: C86.1, D38.A, D39.A, J28.VBUS1, J28.VBUS2, U31.4
V_USB3: C116.1, D55.A, D56.A, J40.VBUS1, J40.VBUS2, U43.4
XTALI: C19.2, U7.XI, X1.P$1
XTALI1: C45.2, U18.XI, X4.P$1
XTALI2: C75.2, U30.XI, X6.P$1
XTALI3: C105.2, U42.XI, X8.P$1
XTALO: C18.2, U7.XO, X1.P$2
XTALO1: C44.2, U18.XO, X4.P$2
XTALO2: C74.2, U30.XO, X6.P$2
XTALO3: C104.2, U42.XO, X8.P$2

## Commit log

2021-09-13 Logos swapped for SFE, proposed antenna switch logic circuit in SCH
2021-09-13 swapping names of U11 and U12 to avoid confusion
2021-09-13 removed voltage divider (logic shift) from inverter to AND gate.
    The AND gate is 5.5V tolerant, so we don't need to shift logic level
2021-09-13 powering U11 from 3.3V
2021-09-13 schematic tightening and moving most to first sheet
2021-09-15 antenna switch circuit added in
    -added antenna switch protection circuit.
    -a few parts moved to 0402 packages to make room
2021-09-16 Switched D8 to a P-CH MOSFET
2021-09-16 schematic cleanup/tightening
2021-09-16 silk updates almost done
2021-09-16 silk updates and R1 to 330 for brighter green power led
2021-09-17 backup battery charge resistor val and switch
    -added pch mosfet to switch backup battery charging on and off via GPIO on artemis
    -changed backup battery charge source to 3.3V rail, and changed charge resistor to 3.3K
    -Moved Iridium module and artemis module down 0.1 inch to allow more clearance around sam-tech connector so epoxy is less likely to flow over/into nearby additional supercap pth pads.
    -moved a few other components from 0603 to 0402 to make more room.
2021-09-22 Reverted back to battery input diode
2021-09-22 Moved all 0.1uF caps to higher spec'd part
2021-09-22 Moved all 1.0uF caps to higher spec'd part
2021-09-22 Moved C25 to 0805 higher voltage rating
    -to decrease BOM diversity
2021-09-23 Routed 8 more Artemis GPIOs to PTH headers
    -routed AD32, D43, D42, AD31, AD29, AD11, D15 and AD12 to 0.1" PTH headers on upper right edge of board.
    -removed full size sparkfun logo, added large flame.
2021-09-23 Broke out D37 to bottom right corner PTH header
2021-09-23 checklist stuff pre-review
    -library work
    -voltage input max in sch
2021-09-23 added measures
2021-09-24 More Gnd vias near AD31 and upper left corner to stitch GND a bit better
    -added more gnd vias near AD31 header to stich ground better
    -nudged traces in upper left away from standoff to make more room for gnd plane, added a couple more vias to connect to bottom pour
2021-09-24 Corrected PROD_ID on ADM4210-1 inrush current detector IC
2021-09-24 design review changes
    -measures cleaned up to avoid overlap
    -LED labels to text only (and corrected 9603N typo)
    -3.3V voltage regulator text in schematic (section label)
    -corrected SPI SCK label on bottom
    -D35 buzzard label turned to AD35 and round end
    -D4 to round end label
2021-09-24 eng checklist run
    nudged some vias to avoid hitting silk labels
    -fixed some PROD_IDs
    -a little SCH cleaning
2021-09-24 Production panel and gerbers v10b
2021-10-25 R9 Current Sense Resistor Value changed to 15mOhm
    Switched in-rush current sense resistor from 12mOhms to 15mOhms. This value is easier to source. It changes the in-rush current sense from 4.2A to 3.3A.
    Also added datasheet for in-rush current protection IC: ADM4210
2021-10-25 Updated current sense resistors on production panel to 0.015Ohms (RES-16305)
    updated values and prod_ids on all four boards in the panel
2021-11-10 Bringing over Arduino Examples and more from SPX repo
2021-11-12 GNSS backup battery charging control - added into examples
    Note, by default, most examples (that utilize the GNSS) have GNSS backup battery charging disabled during setup, and then enabled during the "run" portion of the example.
2021-11-12 updating stuff in production test example 17
2021-11-15 Ex17 production test SDA/SCL swap
2021-11-18 AND Gate (U12) PROD_ID update to correct package
2021-11-22 AND Gate (U12) PROD_ID update to correct package on PANEL FILE
    Note, updated both PROD ID and part value on each part of the panel.
2021-11-22 R31 20K 0402 Resistor change
    R31 has been changed from RES-15131 to RES14972, due to supply chain issues.
2021-11-24 Dimensional PDFs,PNGs, and eagle renderings of top/bottom
2021-11-30 Update README.md
    Updating README.md for release.
2021-12-01 Updating ARTEMIS_PINS.md
    Update ARTEMIS_PINS.md with new GPIO PTH connections.
2022-02-03 Adding a KiCAD template for a hookup board connected by pin headers to all broken-out pins of the AGT
2022-04-07 u-blox typo correction
2022-08-20 Adding option to encode and send binary messages in message translator tool
2022-08-20 Updating documentation for message translator tool
2022-09-14 Retries of initialization of PTH sensor now in loop instead of duplicate code
